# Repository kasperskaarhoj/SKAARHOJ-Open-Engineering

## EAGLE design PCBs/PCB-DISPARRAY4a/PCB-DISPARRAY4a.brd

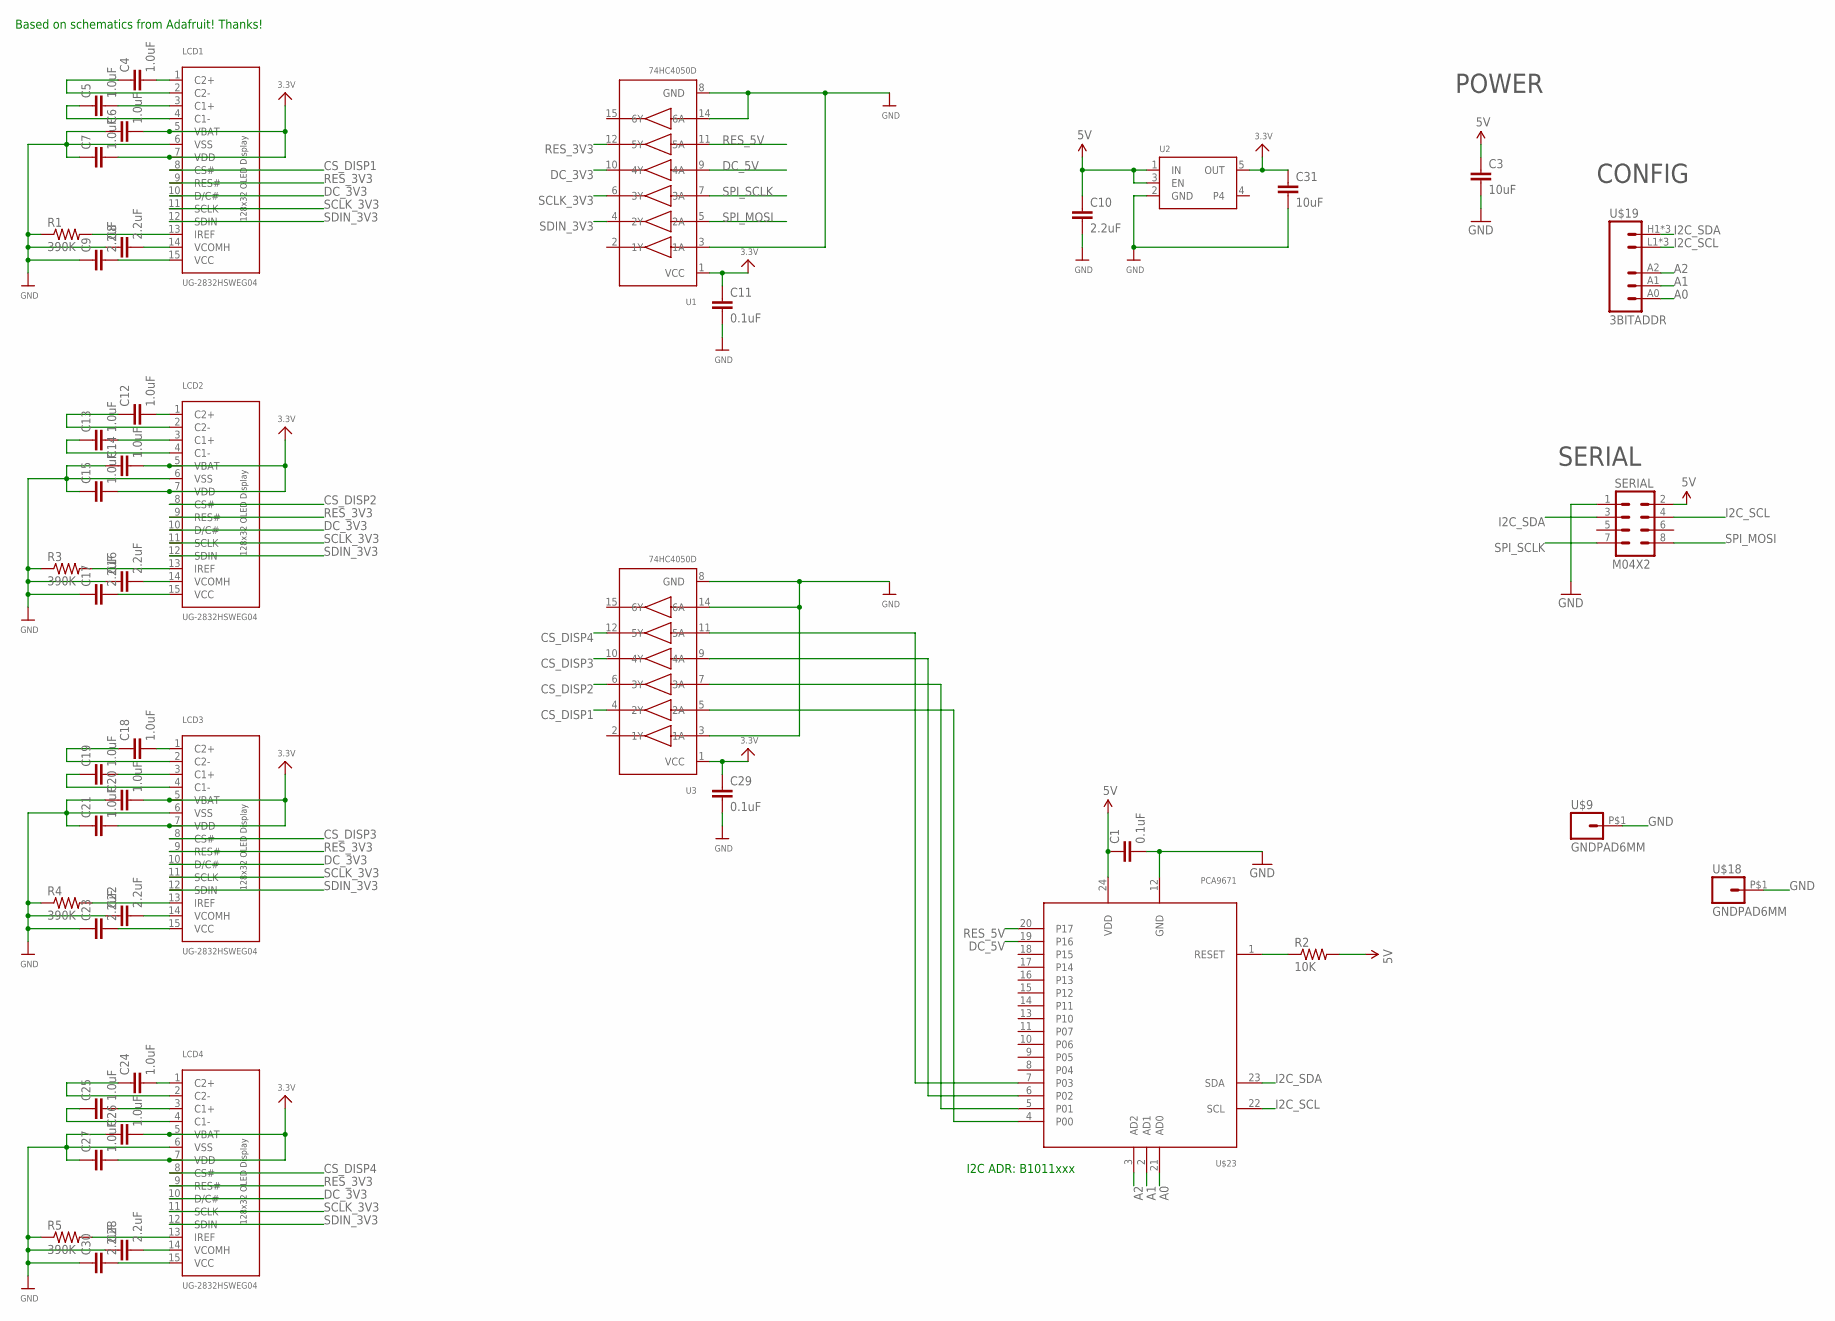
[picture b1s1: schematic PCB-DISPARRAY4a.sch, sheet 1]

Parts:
C1, C11, C29: 0.1uF; 0603-CAP
C3, C31: 10uF; 0805
C4, C5, C6, C7, C12, C13, C14, C15, C18, C19, C20, C21, C24, C25, C26, C27: 1.0uF; 0603-CAP
C8, C9, C16, C17, C22, C23, C28, C30: 2.2uF; 0603-CAP
C10: 2.2uF; 0805
LCD1, LCD2, LCD3, LCD4: UG-2832HSWEG04; UG-2832HSWEG04_WRAPAROUND
R1, R3, R4, R5: 390K; 0603-RES
R2: 10K; 0603-RES
SERIAL: M04X2; 2X4
U1, U3: 74HC4050D; TSSOP16
U2: VREG_SOT23-5; SOT23-5
U$9, U$18: GNDPAD6MM; 3.2MMPAD6MM
U$19: 3BITADDR
U$23: PCA9671; TSSOP24

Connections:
3.3V: C6.2, C7.2, C11.1, C14.2, C15.2, C20.2, C21.2, C26.2, C27.2, C29.1, C31.1, LCD1.5 (VBAT), LCD1.7 (VDD), LCD2.5 (VBAT), LCD2.7 (VDD), LCD3.5 (VBAT), LCD3.7 (VDD), LCD4.5 (VBAT), LCD4.7 (VDD), U1.1 (VCC), U2.5 (OUT), U3.1 (VCC)
5V: C1.1, C3.1, C10.1, R2.2, SERIAL.2, U2.1 (IN), U2.3 (EN), U$23.24 (VDD)
A0: U$19.A0, U$23.21 (AD0)
A1: U$19.A1, U$23.2 (AD1)
A2: U$19.A2, U$23.3 (AD2)
CS_DISP1: LCD1.8 (CS#), U3.4 (2Y)
CS_DISP2: LCD2.8 (CS#), U3.6 (3Y)
CS_DISP3: LCD3.8 (CS#), U3.10 (4Y)
CS_DISP4: LCD4.8 (CS#), U3.12 (5Y)
DC_3V3: LCD1.10 (D/C#), LCD2.10 (D/C#), LCD3.10 (D/C#), LCD4.10 (D/C#), U1.10 (4Y)
DC_5V: U1.9 (4A), U$23.19 (P16)
GND: C1.2, C3.2, C6.1, C7.1, C8.1, C9.1, C10.2, C11.2, C14.1, C15.1, C16.1, C17.1, C20.1, C21.1, C22.1, C23.1, C26.1, C27.1, C28.1, C29.2, C30.1, C31.2, LCD1.6 (VSS), LCD2.6 (VSS), LCD3.6 (VSS), LCD4.6 (VSS), R1.1, R3.1, R4.1, R5.1, SERIAL.1, U1.3 (1A), U1.8 (GND), U1.14 (6A), U2.2 (GND), U3.3 (1A), U3.8 (GND), U3.14 (6A), U$9.P$1, U$18.P$1, U$23.12 (GND)
I2C_SCL: SERIAL.4, U$19.L1 (GND), U$19.L2 (GND), U$19.L3 (GND), U$23.22 (SCL)
I2C_SDA: SERIAL.3, U$19.H1 (VCC), U$19.H2 (VCC), U$19.H3 (VCC), U$23.23 (SDA)
unnamed: R2.1, U$23.1 (RESET)
unnamed: C4.1, LCD1.2 (C2-)
unnamed: C4.2, LCD1.1 (C2+)
unnamed: C5.1, LCD1.4 (C1-)
unnamed: C12.1, LCD2.2 (C2-)
unnamed: C12.2, LCD2.1 (C2+)
unnamed: C5.2, LCD1.3 (C1+)
unnamed: LCD1.13 (IREF), R1.2
unnamed: C8.2, LCD1.14 (VCOMH)
unnamed: C13.1, LCD2.4 (C1-)
unnamed: C13.2, LCD2.3 (C1+)
unnamed: LCD2.13 (IREF), R3.2
unnamed: C16.2, LCD2.14 (VCOMH)
unnamed: C17.2, LCD2.15 (VCC)
unnamed: C18.1, LCD3.2 (C2-)
unnamed: C18.2, LCD3.1 (C2+)
unnamed: C19.1, LCD3.4 (C1-)
unnamed: C19.2, LCD3.3 (C1+)
unnamed: LCD3.13 (IREF), R4.2
unnamed: C22.2, LCD3.14 (VCOMH)
unnamed: C23.2, LCD3.15 (VCC)
unnamed: C24.1, LCD4.2 (C2-)
unnamed: C24.2, LCD4.1 (C2+)
unnamed: C25.1, LCD4.4 (C1-)
unnamed: C25.2, LCD4.3 (C1+)
unnamed: LCD4.13 (IREF), R5.2
unnamed: C28.2, LCD4.14 (VCOMH)
unnamed: C9.2, LCD1.15 (VCC)
unnamed: U3.5 (2A), U$23.4 (P00)
unnamed: U3.7 (3A), U$23.5 (P01)
unnamed: U3.9 (4A), U$23.6 (P02)
unnamed: U3.11 (5A), U$23.7 (P03)
unnamed: C30.2, LCD4.15 (VCC)
RES_3V3: LCD1.9 (RES#), LCD2.9 (RES#), LCD3.9 (RES#), LCD4.9 (RES#), U1.12 (5Y)
RES_5V: U1.11 (5A), U$23.20 (P17)
SCLK_3V3: LCD1.11 (SCLK), LCD2.11 (SCLK), LCD3.11 (SCLK), LCD4.11 (SCLK), U1.6 (3Y)
SDIN_3V3: LCD1.12 (SDIN), LCD2.12 (SDIN), LCD3.12 (SDIN), LCD4.12 (SDIN), U1.4 (2Y)
SPI_MOSI: SERIAL.8, U1.5 (2A)
SPI_SCLK: SERIAL.7, U1.7 (3A)

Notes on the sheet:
I2C ADR: B1011xxx
SERIAL
POWER
CONFIG
Based on schematics from Adafruit! Thanks!

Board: 2 copper layers, 47 parts (41 on the bottom side), 53 nets, no tracks yet.

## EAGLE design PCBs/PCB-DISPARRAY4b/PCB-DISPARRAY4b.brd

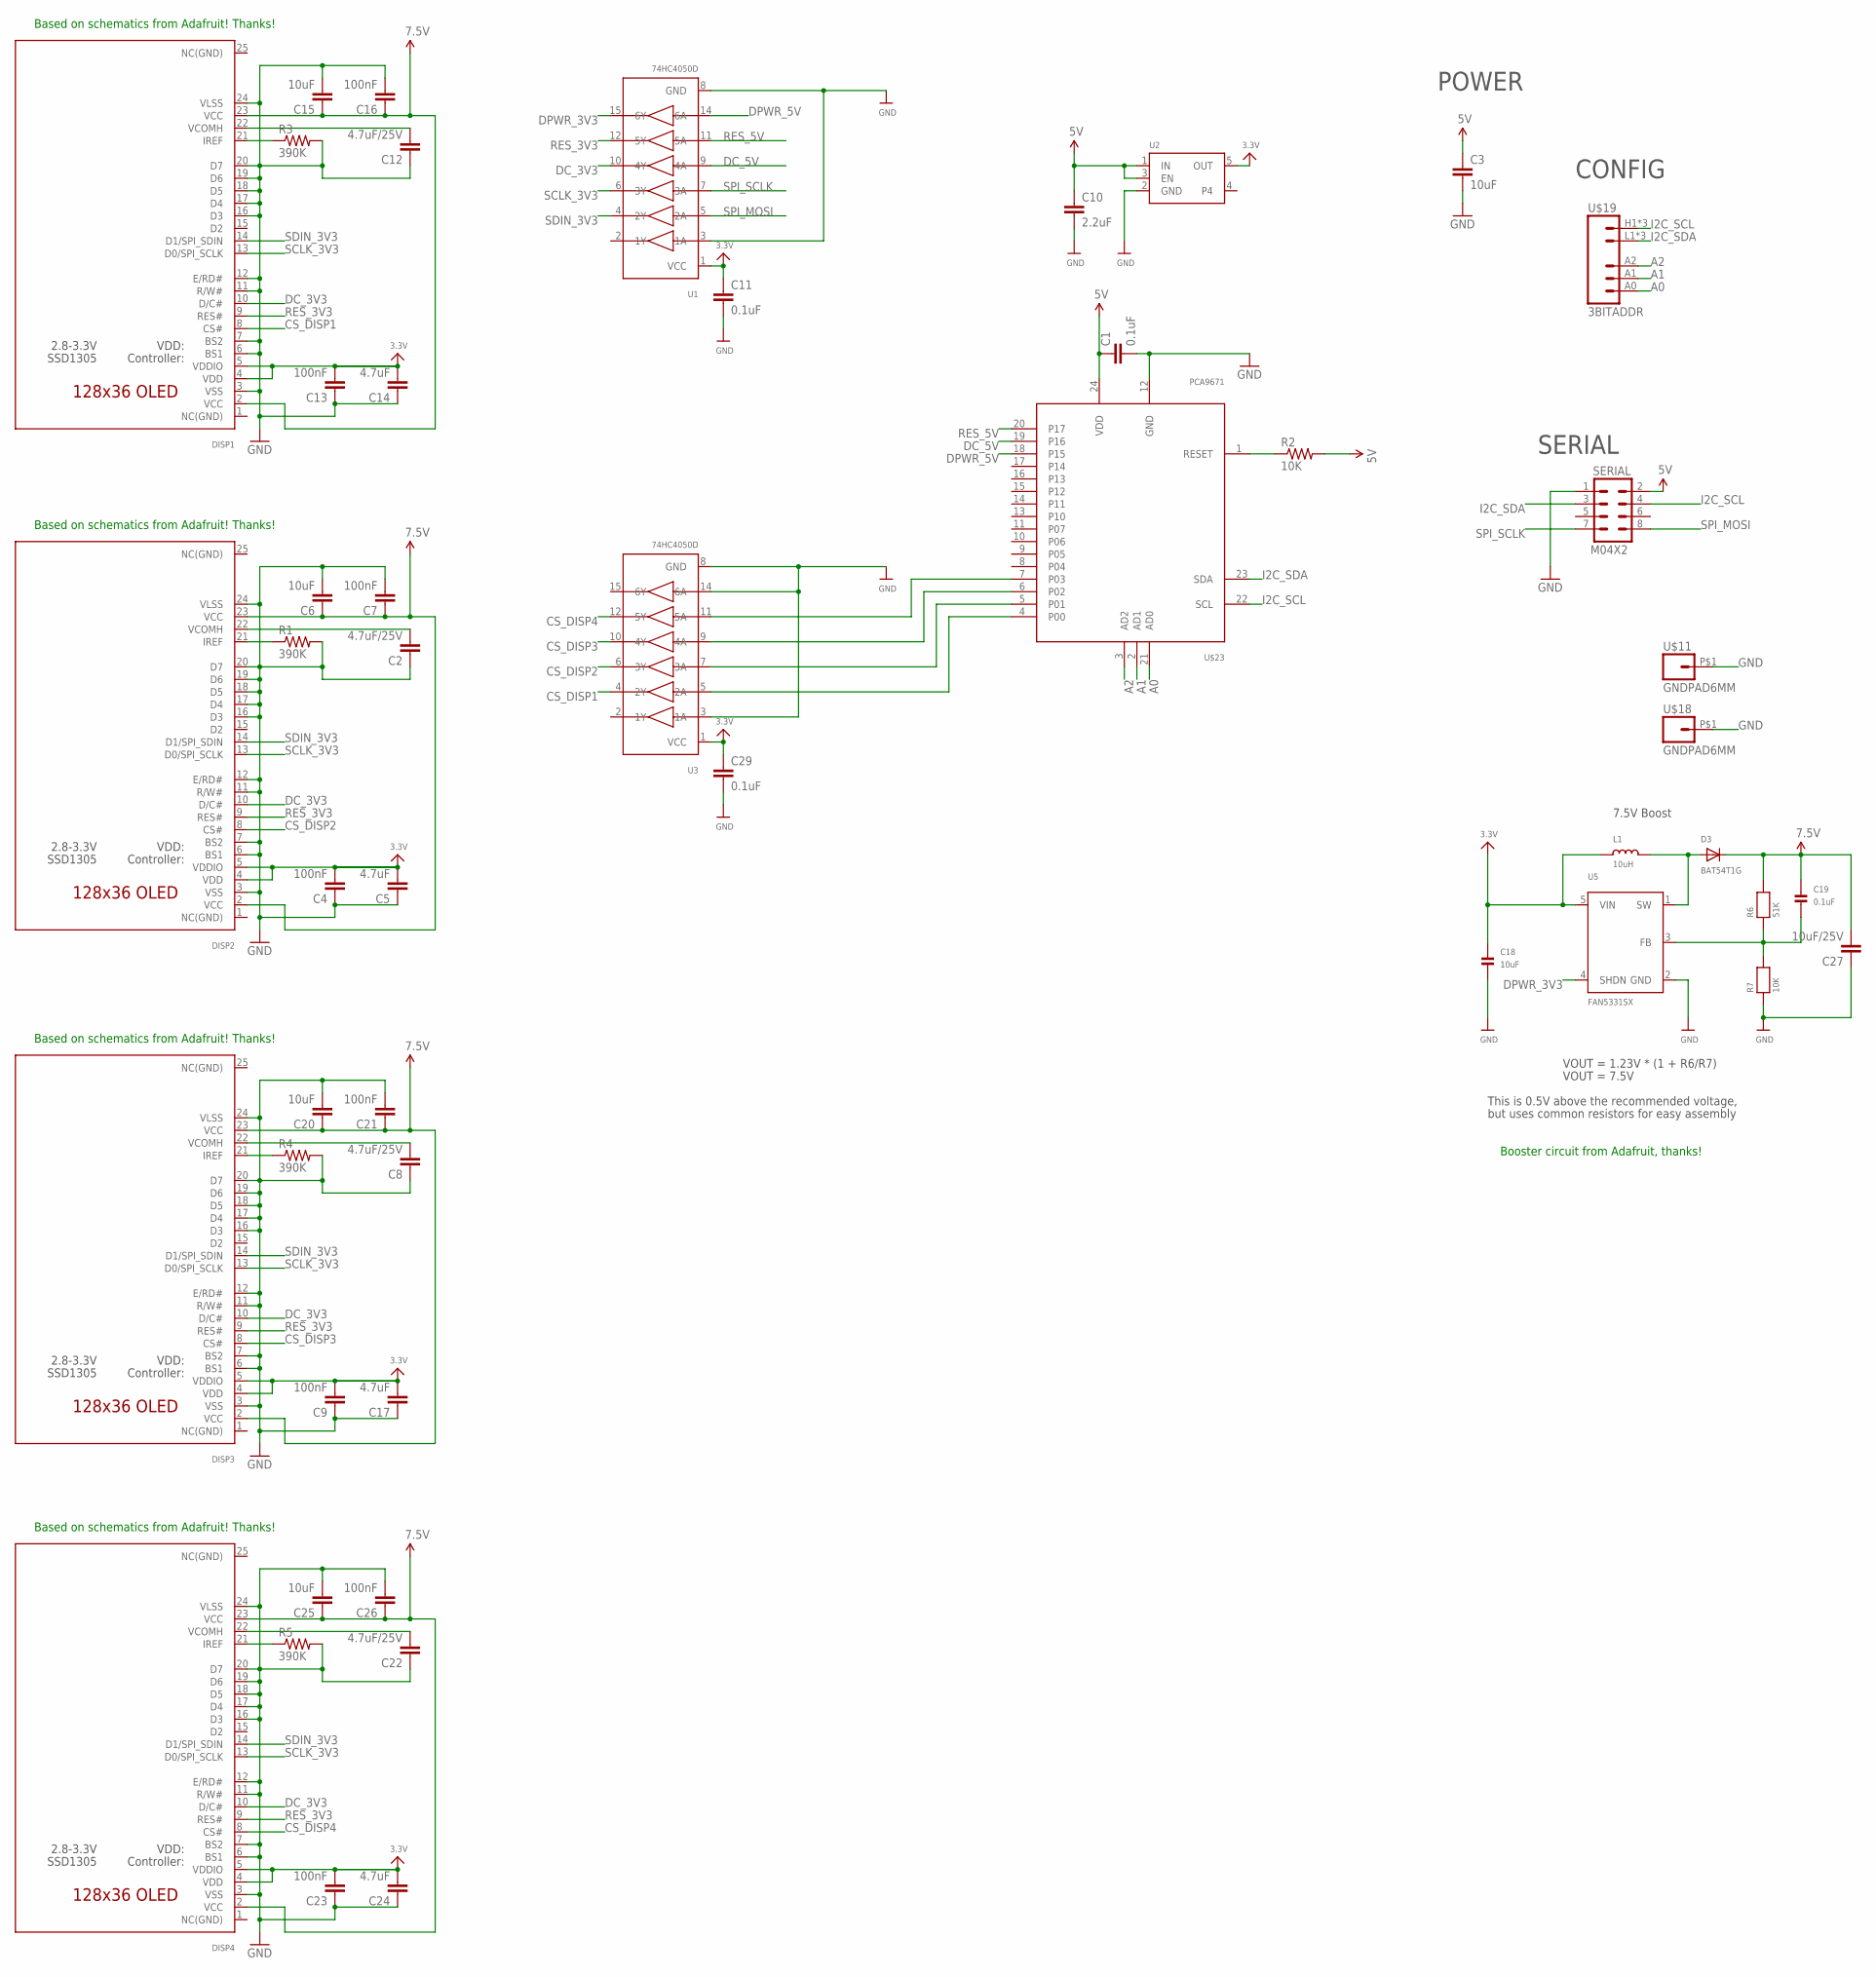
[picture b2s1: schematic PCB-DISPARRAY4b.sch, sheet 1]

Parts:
C1, C11, C29: 0.1uF; 0603-CAP
C2, C8, C12, C22: 4.7uF/25V; 0805
C3, C6, C15, C18, C20, C25: 10uF; 0805
C4, C7, C9, C13, C16, C21, C23, C26: 100nF; 0603-CAP
C5, C14, C17, C24: 4.7uF; 0603-CAP
C10: 2.2uF; 0603-CAP
C19: 0.1uF; 0603
C27: 10uF/25V; 0805
D3: BAT54T1G; SOD-123
DISP1, DISP2, DISP3, DISP4: ER-OLED011-1TOP; ER-OLED011-1
L1: 10uH; INDUCTOR_1007
R1, R3, R4, R5: 390K; 0603-RES
R2: 10K; 0603-RES
R6: 51K; 0603
R7: 10K; 0603
SERIAL: M04X2; 2X4
U1, U3: 74HC4050D; TSSOP16
U2: VREG_SOT23-5; SOT23-5
U5: FAN5331SX; SOT23-5
U$11, U$18: GNDPAD6MM; 3.2MMPAD6MM
U$19: 3BITADDR
U$23: PCA9671; TSSOP24

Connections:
3.3V: C4.2, C5.2, C9.2, C11.1, C13.2, C14.2, C17.2, C18.1, C23.2, C24.2, C29.1, DISP1.4 (VDD), DISP1.5 (VDDIO), DISP2.4 (VDD), DISP2.5 (VDDIO), DISP3.4 (VDD), DISP3.5 (VDDIO), DISP4.4 (VDD), DISP4.5 (VDDIO), L1.P$1 (1), U1.1 (VCC), U2.5 (OUT), U3.1 (VCC), U5.5 (VIN)
5V: C1.1, C3.1, C10.1, R2.2, SERIAL.2, U2.1 (IN), U2.3 (EN), U$23.24 (VDD)
7.5V: C6.1, C7.1, C15.1, C16.1, C19.1, C20.1, C21.1, C25.1, C26.1, C27.2, D3.C, DISP1.2 (VCC), DISP1.23 (VCC), DISP2.2 (VCC), DISP2.23 (VCC), DISP3.2 (VCC), DISP3.23 (VCC), DISP4.2 (VCC), DISP4.23 (VCC), R6.2
A0: U$19.A0, U$23.21 (AD0)
A1: U$19.A1, U$23.2 (AD1)
A2: U$19.A2, U$23.3 (AD2)
CS_DISP1: DISP1.8 (CS#), U3.4 (2Y)
CS_DISP2: DISP2.8 (CS#), U3.6 (3Y)
CS_DISP3: DISP3.8 (CS#), U3.10 (4Y)
CS_DISP4: DISP4.8 (CS#), U3.12 (5Y)
DC_3V3: DISP1.10 (D/C#), DISP2.10 (D/C#), DISP3.10 (D/C#), DISP4.10 (D/C#), U1.10 (4Y)
DC_5V: U1.9 (4A), U$23.19 (P16)
DPWR_3V3: U1.15 (6Y), U5.4 (SHDN)
DPWR_5V: U1.14 (6A), U$23.18 (P15)
GND: C1.2, C2.1, C3.2, C4.1, C5.1, C6.2, C7.2, C8.1, C9.1, C10.2, C11.2, C12.1, C13.1, C14.1, C15.2, C16.2, C17.1, C18.2, C20.2, C21.2, C22.1, C23.1, C24.1, C25.2, C26.2, C27.1, C29.2, DISP1.3 (VSS), DISP1.6 (BS1), DISP1.7 (BS2), DISP1.11 (R/W#), DISP1.12 (E/RD#), DISP1.16 (D3), DISP1.17 (D4), DISP1.18 (D5), DISP1.19 (D6), DISP1.20 (D7), DISP1.24 (VLSS), DISP2.3 (VSS), DISP2.6 (BS1), DISP2.7 (BS2), DISP2.11 (R/W#), DISP2.12 (E/RD#), DISP2.16 (D3), DISP2.17 (D4), DISP2.18 (D5), DISP2.19 (D6), DISP2.20 (D7), DISP2.24 (VLSS), DISP3.3 (VSS), DISP3.6 (BS1), DISP3.7 (BS2), DISP3.11 (R/W#), DISP3.12 (E/RD#), DISP3.16 (D3), DISP3.17 (D4), DISP3.18 (D5), DISP3.19 (D6), DISP3.20 (D7), DISP3.24 (VLSS), DISP4.3 (VSS), DISP4.6 (BS1), DISP4.7 (BS2), DISP4.11 (R/W#), DISP4.12 (E/RD#), DISP4.16 (D3), DISP4.17 (D4), DISP4.18 (D5), DISP4.19 (D6), DISP4.20 (D7), DISP4.24 (VLSS), R1.2, R3.2, R4.2, R5.2, R7.1, SERIAL.1, U1.3 (1A), U1.8 (GND), U2.2 (GND), U3.3 (1A), U3.8 (GND), U3.14 (6A), U5.2 (GND), U$11.P$1, U$18.P$1, U$23.12 (GND)
I2C_SCL: SERIAL.4, U$19.H1 (VCC), U$19.H2 (VCC), U$19.H3 (VCC), U$23.22 (SCL)
I2C_SDA: SERIAL.3, U$19.L1 (GND), U$19.L2 (GND), U$19.L3 (GND), U$23.23 (SDA)
unnamed: R2.1, U$23.1 (RESET)
unnamed: DISP2.21 (IREF), R1.1
unnamed: C2.2, DISP2.22 (VCOMH)
unnamed: DISP3.21 (IREF), R4.1
unnamed: DISP1.21 (IREF), R3.1
unnamed: C8.2, DISP3.22 (VCOMH)
unnamed: DISP4.21 (IREF), R5.1
unnamed: C22.2, DISP4.22 (VCOMH)
unnamed: C12.2, DISP1.22 (VCOMH)
unnamed: D3.A, L1.P$2 (2), U5.1 (SW)
unnamed: C19.2, R6.1, R7.2, U5.3 (FB)
unnamed: U3.5 (2A), U$23.4 (P00)
unnamed: U3.7 (3A), U$23.5 (P01)
unnamed: U3.9 (4A), U$23.6 (P02)
unnamed: U3.11 (5A), U$23.7 (P03)
RES_3V3: DISP1.9 (RES#), DISP2.9 (RES#), DISP3.9 (RES#), DISP4.9 (RES#), U1.12 (5Y)
RES_5V: U1.11 (5A), U$23.20 (P17)
SCLK_3V3: DISP1.13 (D0/SPI_SCLK), DISP2.13 (D0/SPI_SCLK), DISP3.13 (D0/SPI_SCLK), DISP4.13 (D0/SPI_SCLK), U1.6 (3Y)
SDIN_3V3: DISP1.14 (D1/SPI_SDIN), DISP2.14 (D1/SPI_SDIN), DISP3.14 (D1/SPI_SDIN), DISP4.14 (D1/SPI_SDIN), U1.4 (2Y)
SPI_MOSI: SERIAL.8, U1.5 (2A)
SPI_SCLK: SERIAL.7, U1.7 (3A)

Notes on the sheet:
SERIAL
POWER
CONFIG
Based on schematics from Adafruit! Thanks!
VOUT = 1.23V * (1 + R6/R7)
VOUT = 7.5V
This is 0.5V above the recommended voltage,
but uses common resistors for easy assembly
7.5V Boost
Booster circuit from Adafruit, thanks!

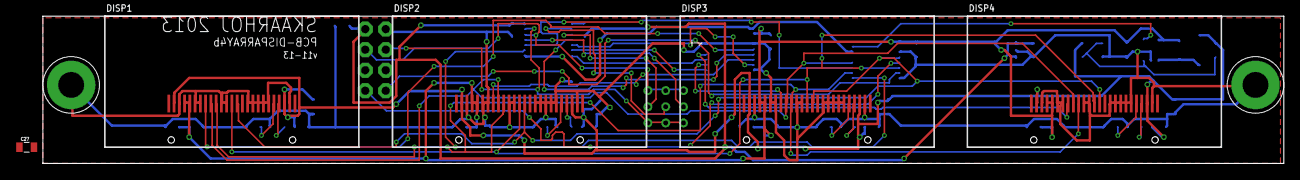
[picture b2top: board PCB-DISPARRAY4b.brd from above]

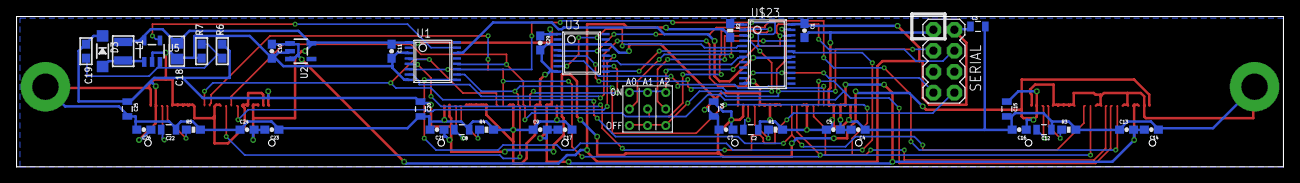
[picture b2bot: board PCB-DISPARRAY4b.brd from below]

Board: 2 copper layers, 153.4 x 18.2 mm, 50 parts (43 on the bottom side), 38 nets.

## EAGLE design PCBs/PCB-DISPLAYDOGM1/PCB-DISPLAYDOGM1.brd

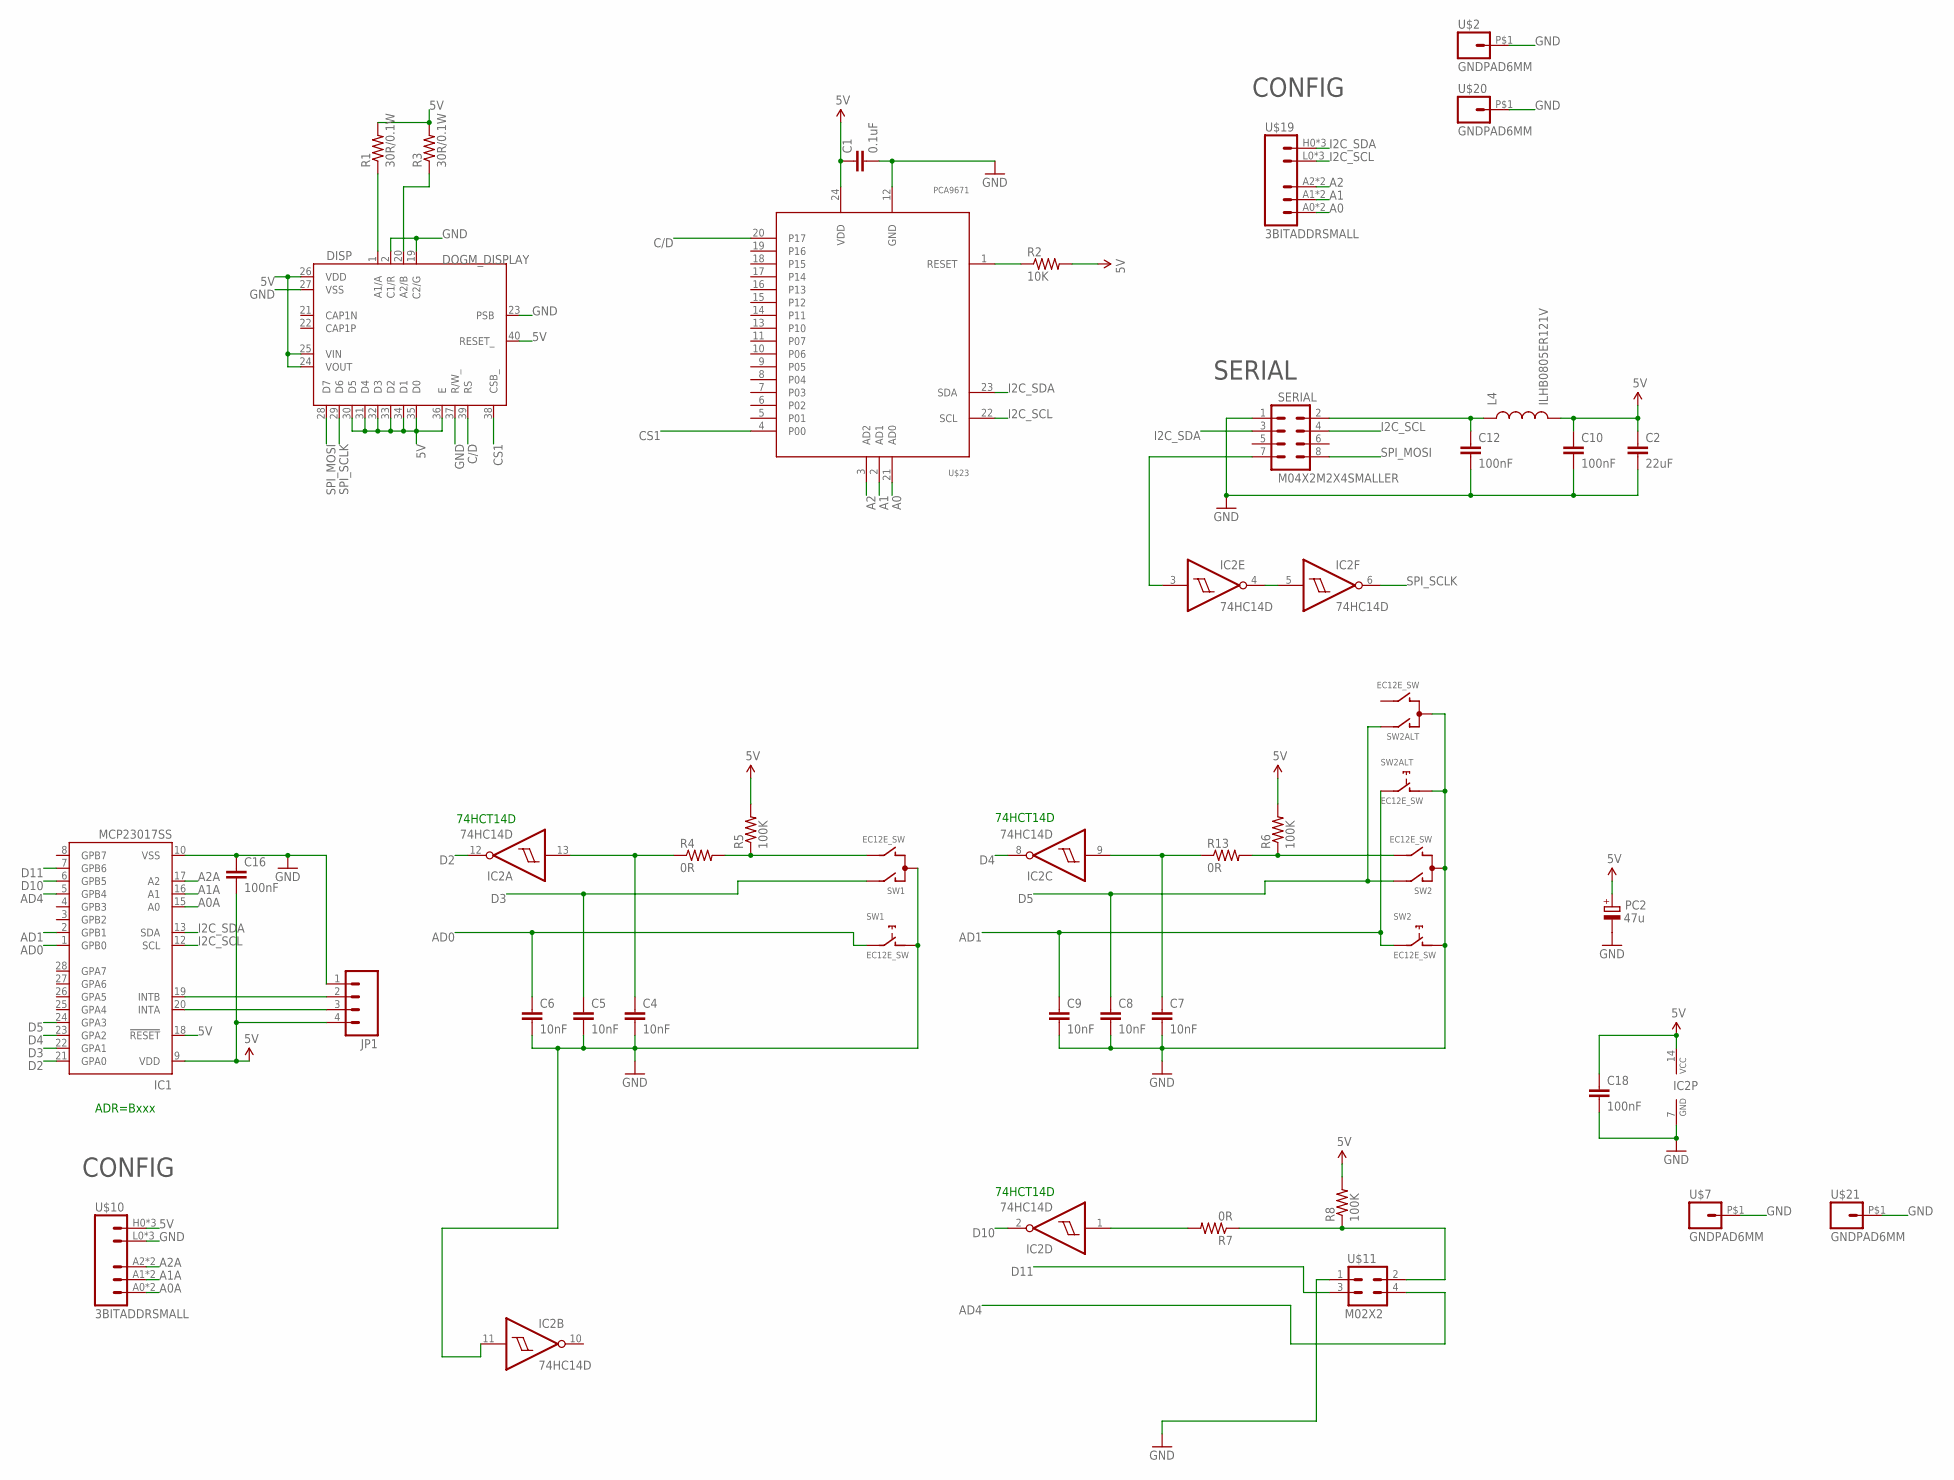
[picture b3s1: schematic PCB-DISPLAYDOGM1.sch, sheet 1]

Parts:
C1: 0.1uF; 0603-CAP
C2: 22uF; 0805
C4, C5, C6, C7, C8, C9: 10nF; 0603-CAP
C10, C12, C16, C18: 100nF; 0603-CAP
DISP: DOGM_DISPLAY; DOGM
IC1: MCP23017SS; SSOP28; MPN MCP23017-E/SS
IC2: 74HC14D; SO14
JP1: M04PTH; 1X04
L4: ILHB0805ER121V; 0805
PC2: 47u; PANASONIC_D
R1, R3: 30R/0.1W; 0603-RES
R2: 10K; 0603-RES
R4, R7, R13: 0R; 0603-RES
R5, R6, R8: 100K; 0603-RES
SERIAL: M04X2M2X4SMALLER; M2X4SMALLER
SW1, SW2, SW2ALT: EC12E_SW; ALPS_EC12E_SW
U$2, U$7, U$20, U$21: GNDPAD6MM; 3.2MMPAD6MM
U$10, U$19: 3BITADDRSMALL; 3BITADDR_SMALL
U$11: M02X2; 2X2
U$23: PCA9671; TSSOP24

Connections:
5V: C1.1, C2.1, C10.1, C16.2, C18.1, DISP.24 (VOUT), DISP.25 (VIN), DISP.26 (VDD), DISP.30 (D5), DISP.31 (D4), DISP.32 (D3), DISP.33 (D2), DISP.34 (D1), DISP.35 (D0), DISP.36 (E), DISP.40 (RESET_), IC1.9 (VDD), IC1.18 (!RESET), IC2.14 (VCC), JP1.4, L4.2, PC2.+, R1.2, R2.2, R3.2, R5.2, R6.2, R8.2, U$10.H0 (VCC), U$10.H1 (VCC), U$10.H2 (VCC), U$23.24 (VDD)
A0: U$19.A0, U$19.AS0 (A0), U$23.21 (AD0)
A0A: IC1.15 (A0), U$10.A0, U$10.AS0 (A0)
A1: U$19.A1, U$19.AS1 (A1), U$23.2 (AD1)
A1A: IC1.16 (A1), U$10.A1, U$10.AS1 (A1)
A2: U$19.A2, U$19.AS2 (A2), U$23.3 (AD2)
A2A: IC1.17 (A2), U$10.A2, U$10.AS2 (A2)
AD0: C6.1, IC1.1 (GPB0), SW1.E (2)
AD1: C9.1, IC1.2 (GPB1), SW2.E (2), SW2ALT.E (2)
AD4: IC1.5 (GPB4), U$11.4
ARD_5V: C12.1, L4.1, SERIAL.2
C/D: DISP.39 (RS), U$23.20 (P17)
CS1: DISP.38 (CSB_), U$23.4 (P00)
D2: IC1.21 (GPA0), IC2.12 (O)
D3: C5.1, IC1.22 (GPA1), SW1.A
D4: IC1.23 (GPA2), IC2.8 (O)
D5: C8.1, IC1.24 (GPA3), SW2.A, SW2ALT.A
D10: IC1.6 (GPB5), IC2.2 (O)
D11: IC1.7 (GPB6), U$11.3
GND: C1.2, C2.2, C4.2, C5.2, C6.2, C7.2, C8.2, C9.2, C10.2, C12.2, C16.1, C18.2, DISP.2 (C1/R), DISP.19 (C2/G), DISP.23 (PSB), DISP.27 (VSS), DISP.37 (R/W_), IC1.10 (VSS), IC2.7 (GND), IC2.11 (I), JP1.1, PC2.-, SERIAL.1, SW1.C, SW1.D (1), SW2.C, SW2.D (1), SW2ALT.C, SW2ALT.D (1), U$2.P$1, U$7.P$1, U$10.L0 (GND), U$10.L1 (GND), U$10.L2 (GND), U$11.1, U$20.P$1, U$21.P$1, U$23.12 (GND)
I2C_SCL: IC1.12 (SCL), SERIAL.4, U$19.L0 (GND), U$19.L1 (GND), U$19.L2 (GND), U$23.22 (SCL)
I2C_SDA: IC1.13 (SDA), SERIAL.3, U$19.H0 (VCC), U$19.H1 (VCC), U$19.H2 (VCC), U$23.23 (SDA)
unnamed: R2.1, U$23.1 (RESET)
unnamed: DISP.1 (A1/A), R1.1
unnamed: DISP.20 (A2/B), R3.1
unnamed: R4.2, R5.1, SW1.B
unnamed: IC2.1 (I), R7.2
unnamed: R6.1, R13.2, SW2.B
unnamed: IC2.4 (O), IC2.5 (I)
unnamed: IC2.3 (I), SERIAL.7
unnamed: IC1.19 (INTB), JP1.2
unnamed: IC1.20 (INTA), JP1.3
unnamed: C4.1, IC2.13 (I), R4.1
unnamed: C7.1, IC2.9 (I), R13.1
unnamed: R7.1, R8.1, U$11.2
SPI_MOSI: DISP.28 (D7), SERIAL.8
SPI_SCLK: DISP.29 (D6), IC2.6 (O)

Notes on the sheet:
SERIAL
CONFIG
ADR=Bxxx
74HCT14D

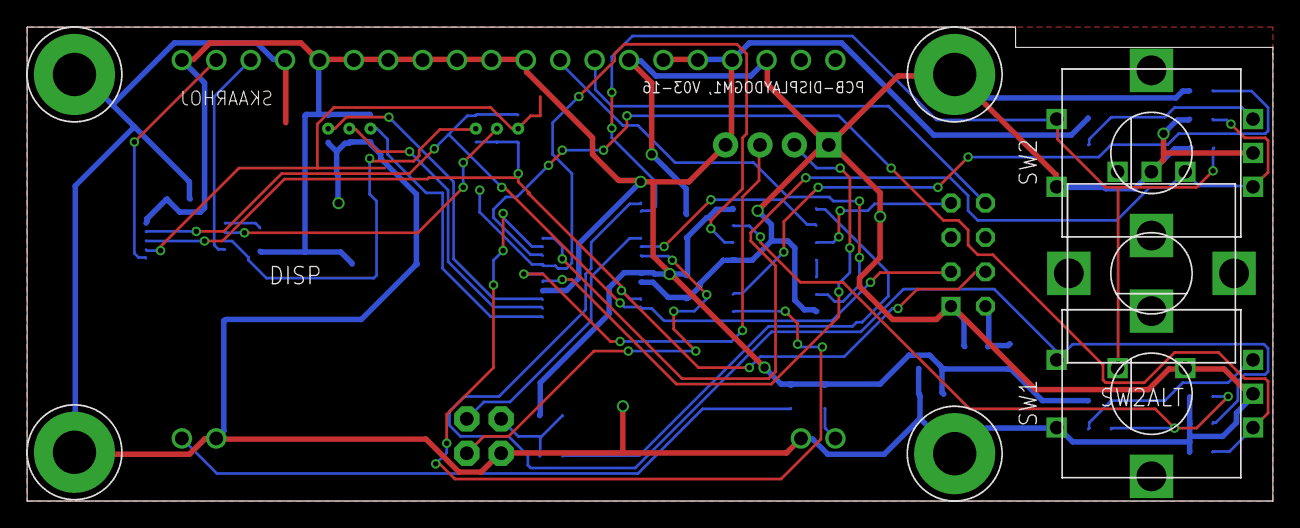
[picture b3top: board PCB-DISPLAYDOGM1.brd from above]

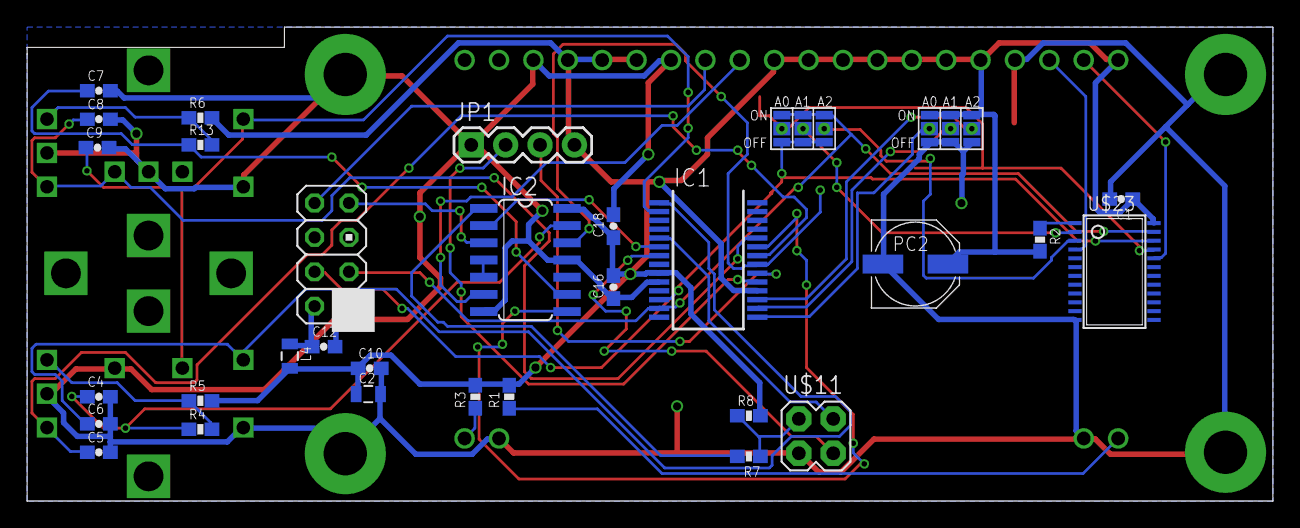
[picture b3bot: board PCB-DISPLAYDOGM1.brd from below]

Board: 2 copper layers, 92.0 x 35.0 mm, 39 parts (31 on the bottom side), 37 nets.

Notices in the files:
parts and their libraries:
SparkFun: Licensing: CC v3.0 Share-Alike You are welcome to use this library for commercial purposes.
